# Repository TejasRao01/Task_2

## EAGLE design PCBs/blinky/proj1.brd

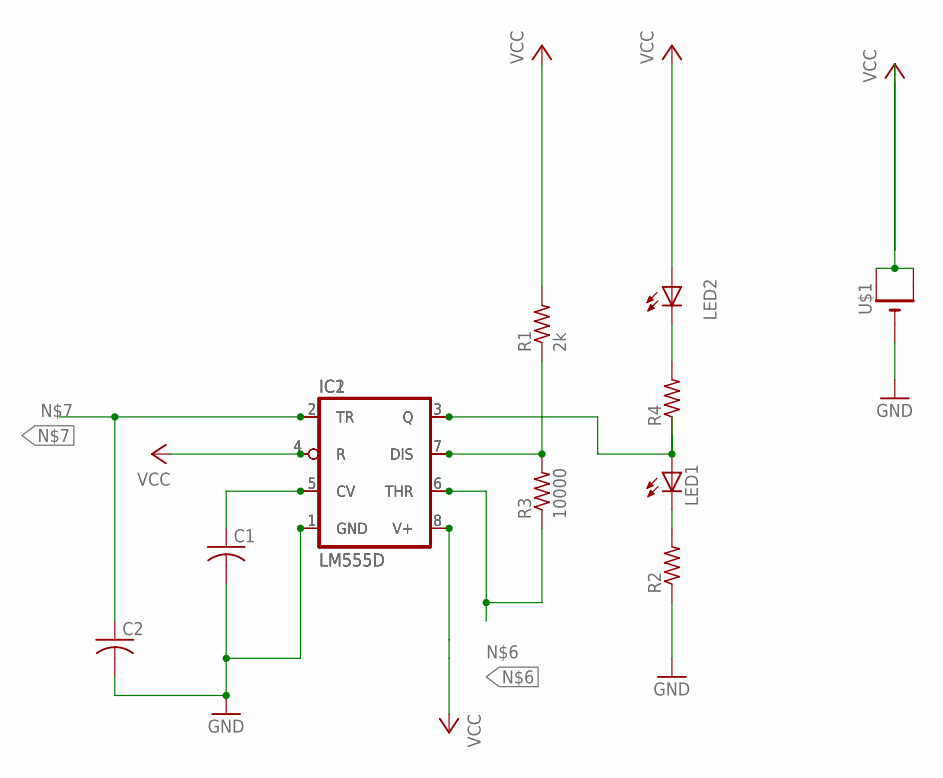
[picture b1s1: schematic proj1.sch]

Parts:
C1, C2: C-USC0805; C0805
IC1, IC2: LM555D; SO08
LED1, LED2: LEDCHIPLED_0805; CHIPLED_0805
R1: 2k; M0805
R2, R4: R-US_M0805; M0805
R3: 10000; M0805
U$1: CR1220SMT; CR1220-SMD

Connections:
GND: C1.2, C2.2, IC1.1 (GND), IC2.1 (GND), R2.1, U$1.-
unnamed: LED2.C, R4.2
unnamed: IC1.3 (Q), IC2.3 (Q), LED1.A, R4.1
unnamed: LED1.C, R2.2
unnamed: C1.1, IC1.5 (CV), IC2.5 (CV)
unnamed: IC1.7 (DIS), IC2.7 (DIS), R1.1, R3.2
unnamed: IC1.6 (THR), IC2.6 (THR), R3.1
unnamed: C2.1, IC1.2 (TR), IC2.2 (TR)
unnamed: IC1.8 (V+), IC2.8 (V+)
VCC: IC1.4 (R), IC2.4 (R), LED2.A, R1.2, U$1.+$1 (+), U$1.+$2 (+1)

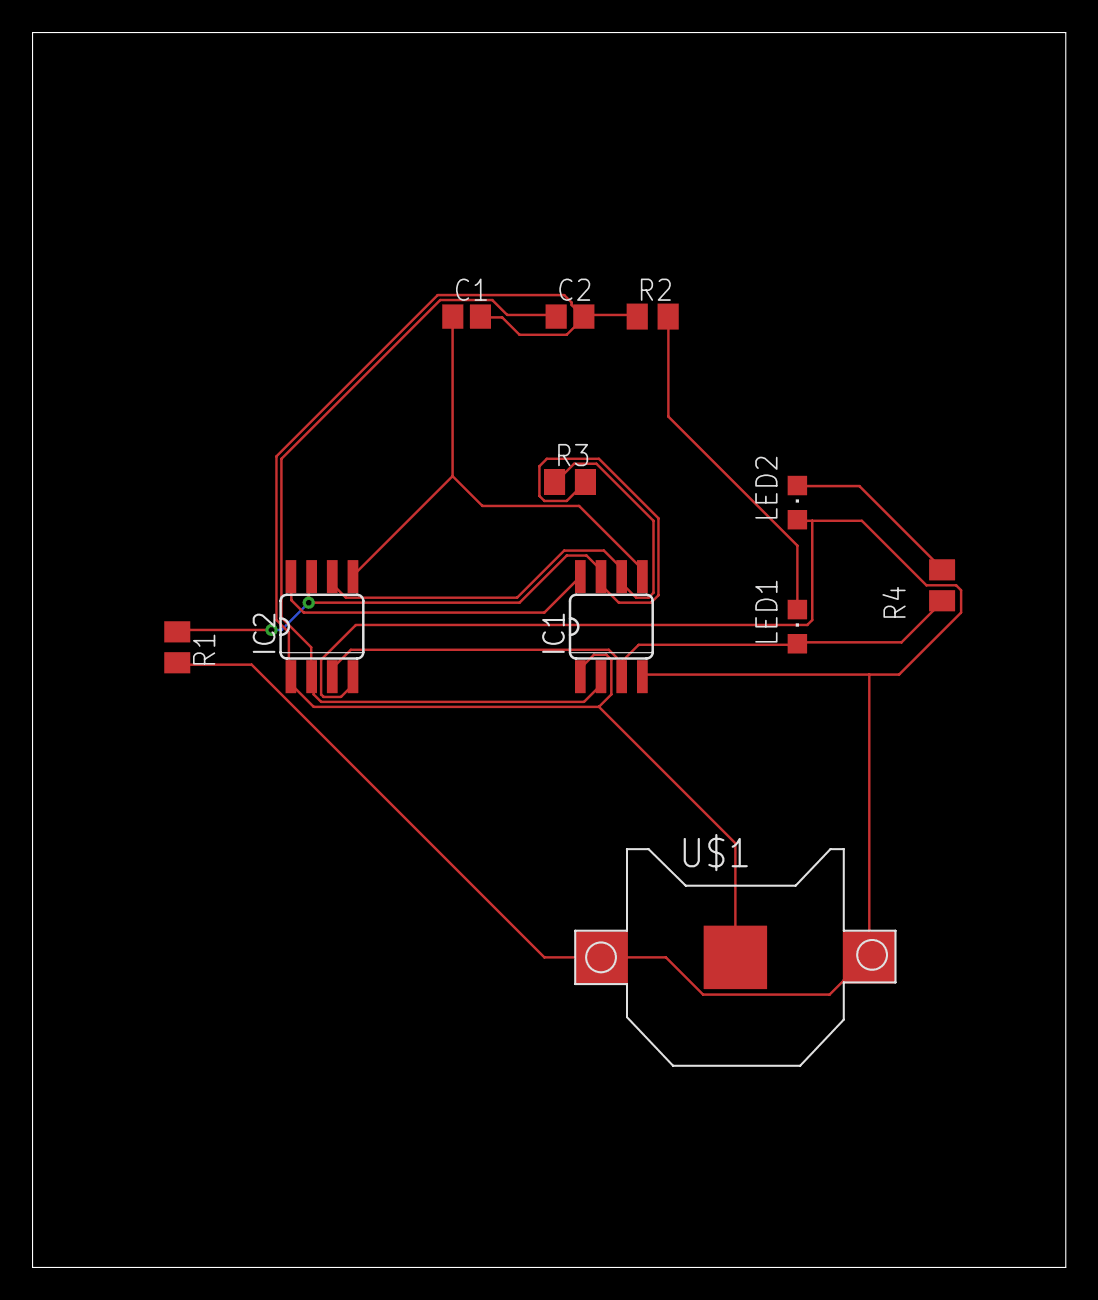
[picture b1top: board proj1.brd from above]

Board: 2 copper layers, 63.5 x 75.9 mm, 11 parts (0 on the bottom side), 10 nets.

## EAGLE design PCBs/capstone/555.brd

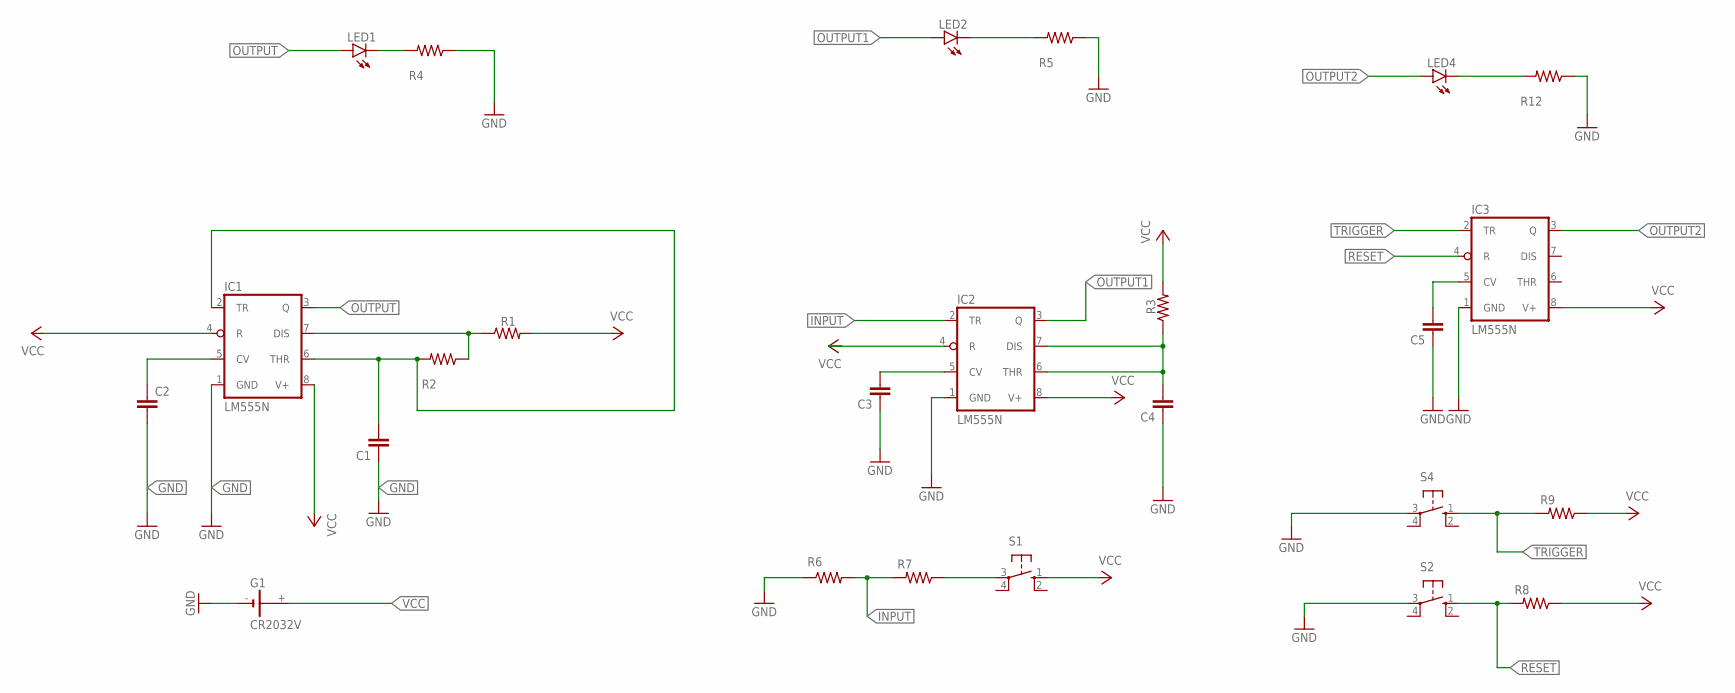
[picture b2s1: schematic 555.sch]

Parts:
C1, C2, C3, C4, C5: C-EU025-025X050; C025-025X050
G1: CR2032V
IC1, IC2, IC3: LM555N; DIL08-ROUND
LED1, LED2, LED4: LED3MM
R1, R2, R3, R4, R5, R6, R7, R8, R9, R12: R-US_R2010; R2010
S1, S2, S4: 10-XX; B3F-10XX

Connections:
GND: C1.1, C2.2, C3.1, C4.1, C5.1, G1.-, IC1.1 (GND), IC2.1 (GND), IC3.1 (GND), R4.1, R5.1, R6.1, R12.1, S2.3, S4.3
INPUT: IC2.2 (TR), R6.2, R7.2
unnamed: C2.1, IC1.5 (CV)
unnamed: C1.2, IC1.2 (TR), IC1.6 (THR), R2.2
unnamed: C4.2, IC2.6 (THR), IC2.7 (DIS), R3.1
unnamed: IC1.7 (DIS), R1.1, R2.1
unnamed: C3.2, IC2.5 (CV)
unnamed: LED2.K (C), R5.2
unnamed: LED1.K (C), R4.2
unnamed: R7.1, S1.3
unnamed: LED4.K (C), R12.2
unnamed: C5.2, IC3.5 (CV)
OUTPUT: IC1.3 (Q), LED1.A
OUTPUT1: IC2.3 (Q), LED2.A
OUTPUT2: IC3.3 (Q), LED4.A
RESET: IC3.4 (R), R8.2, S2.1 (S)
TRIGGER: IC3.2 (TR), R9.2, S4.1 (S)
VCC: G1.+, IC1.4 (R), IC1.8 (V+), IC2.4 (R), IC2.8 (V+), IC3.8 (V+), R1.2, R3.2, R8.1, R9.1, S1.1 (S)

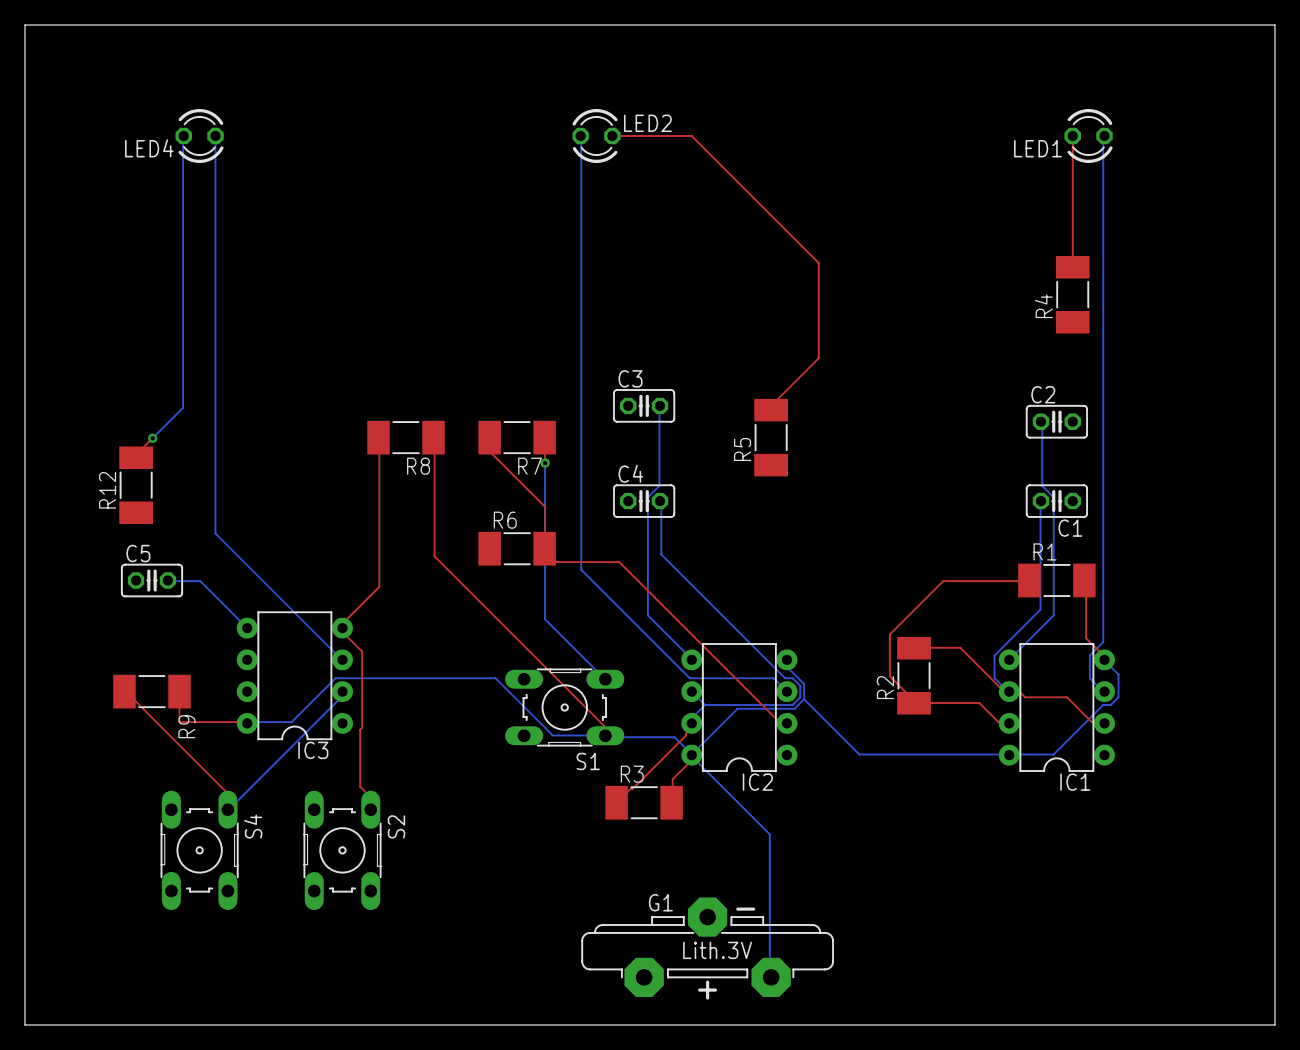
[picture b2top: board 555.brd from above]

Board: 2 copper layers, 100.0 x 80.0 mm, 25 parts (0 on the bottom side), 18 nets.

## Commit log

2021-09-04 Create pcb
2021-09-04 Create tiel
2021-09-05 Create blinky
